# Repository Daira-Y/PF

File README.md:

# PF
Phamaceutical Water Analyzer

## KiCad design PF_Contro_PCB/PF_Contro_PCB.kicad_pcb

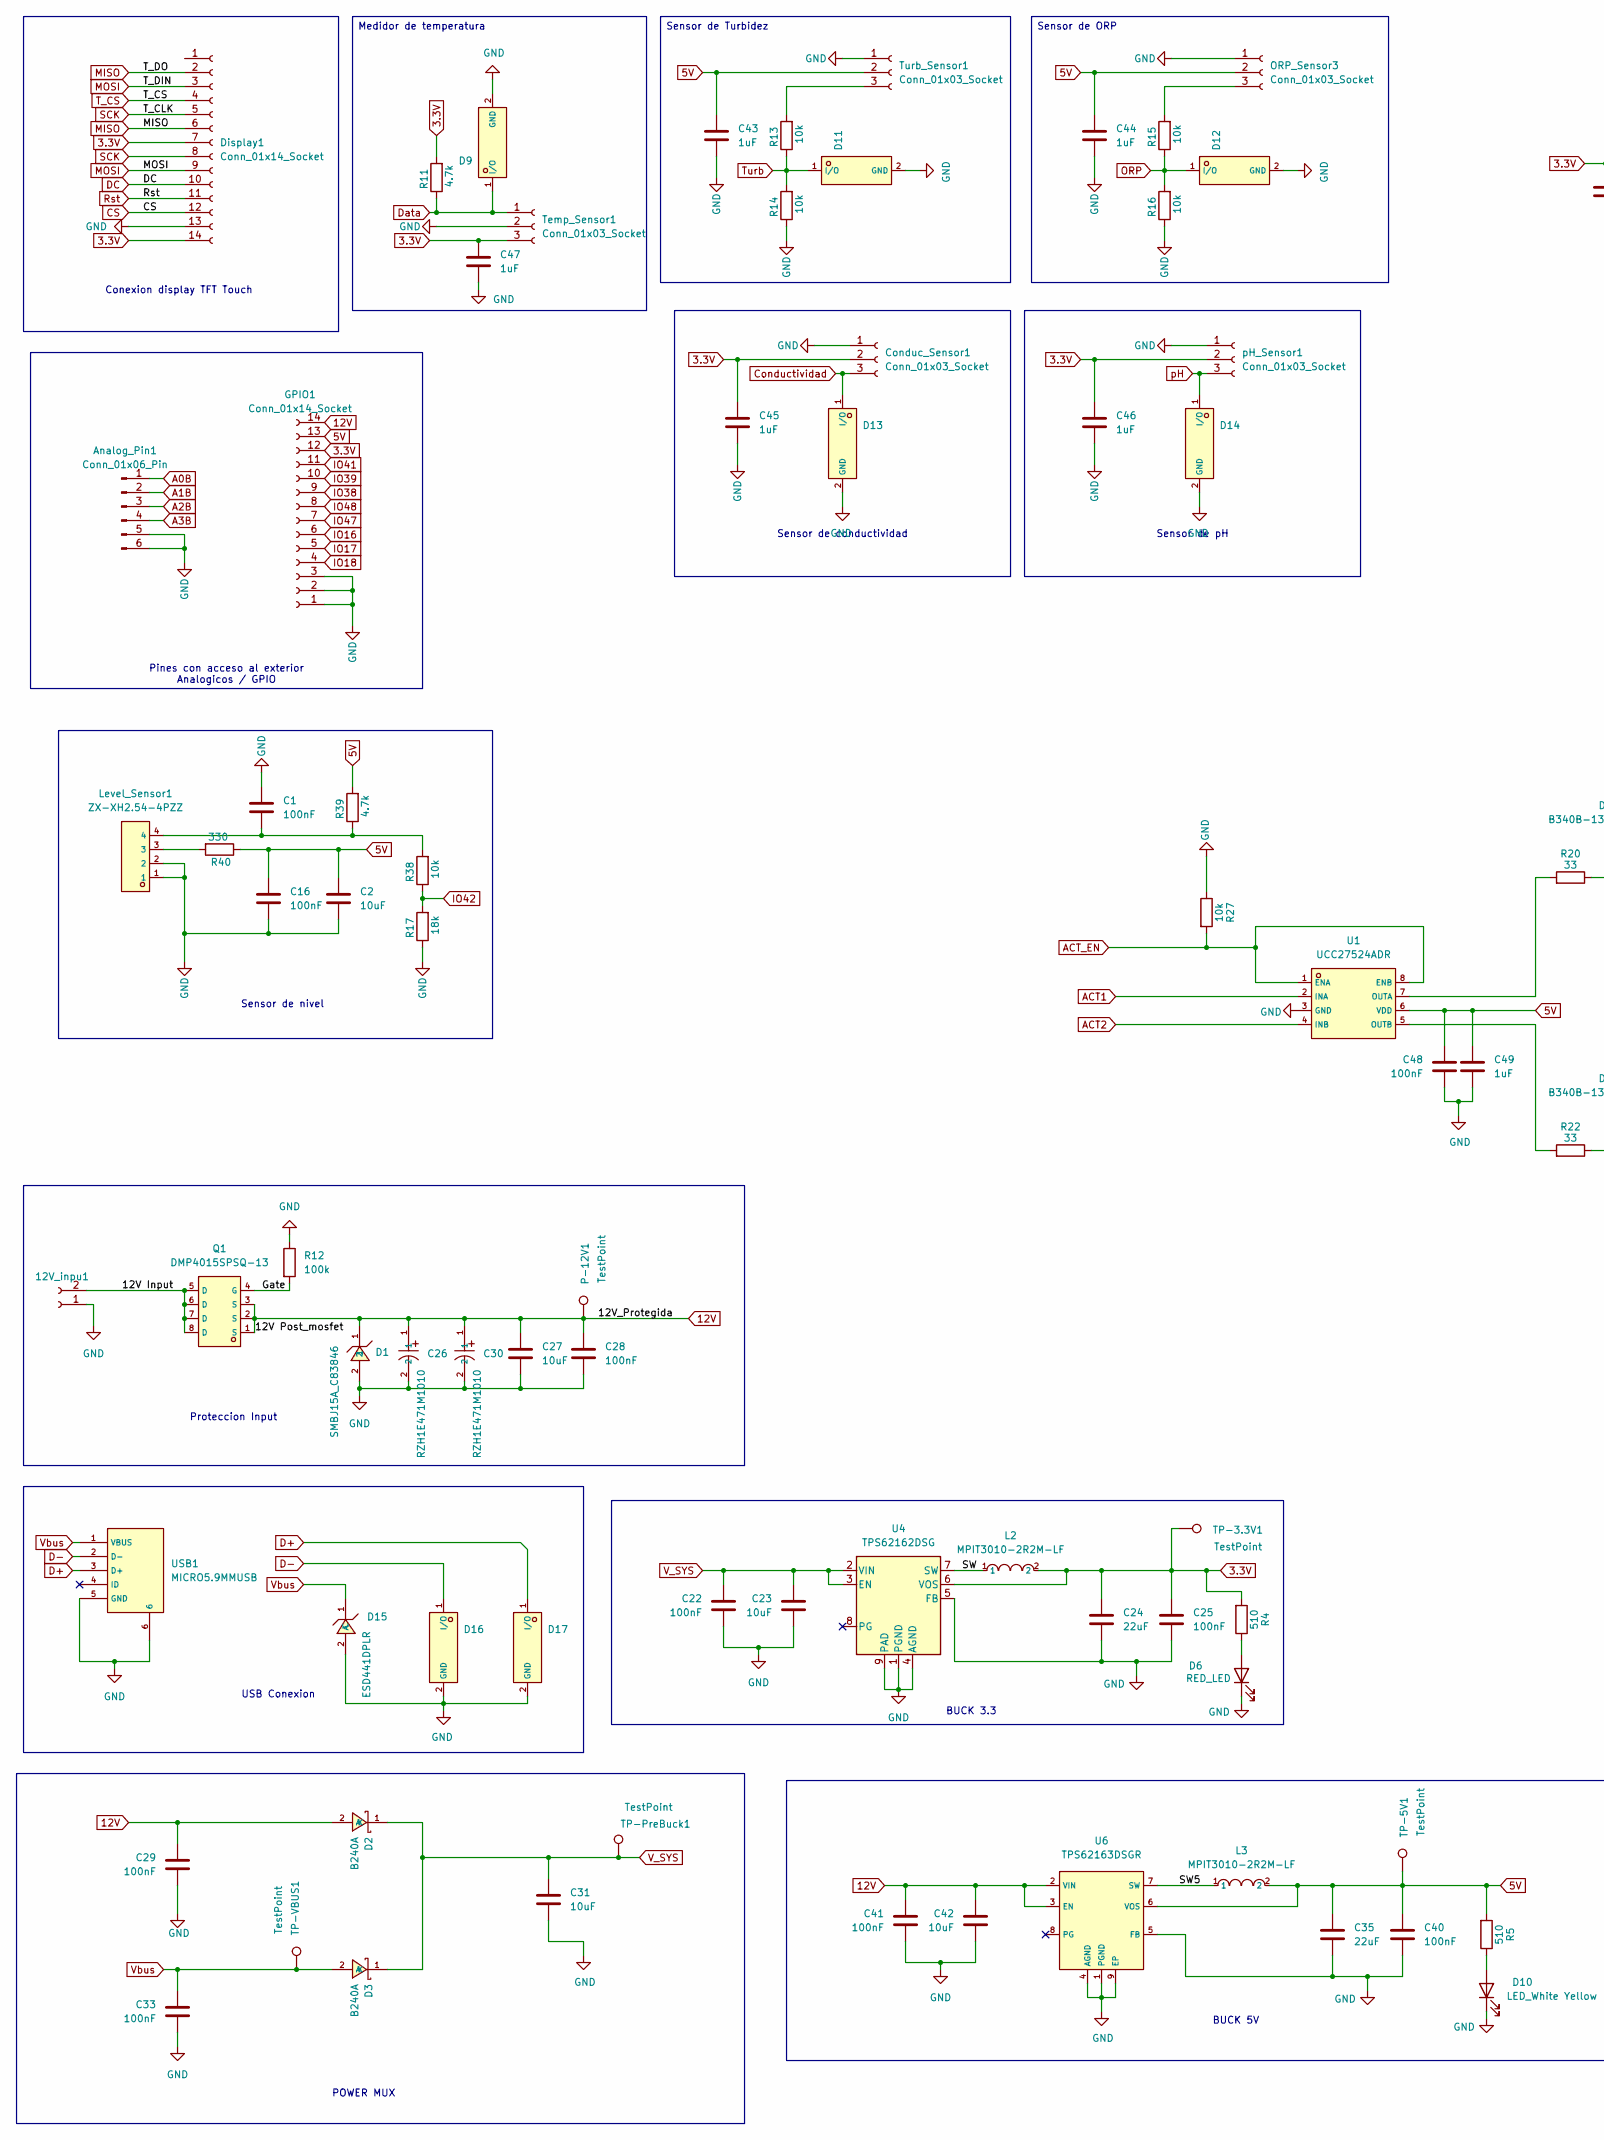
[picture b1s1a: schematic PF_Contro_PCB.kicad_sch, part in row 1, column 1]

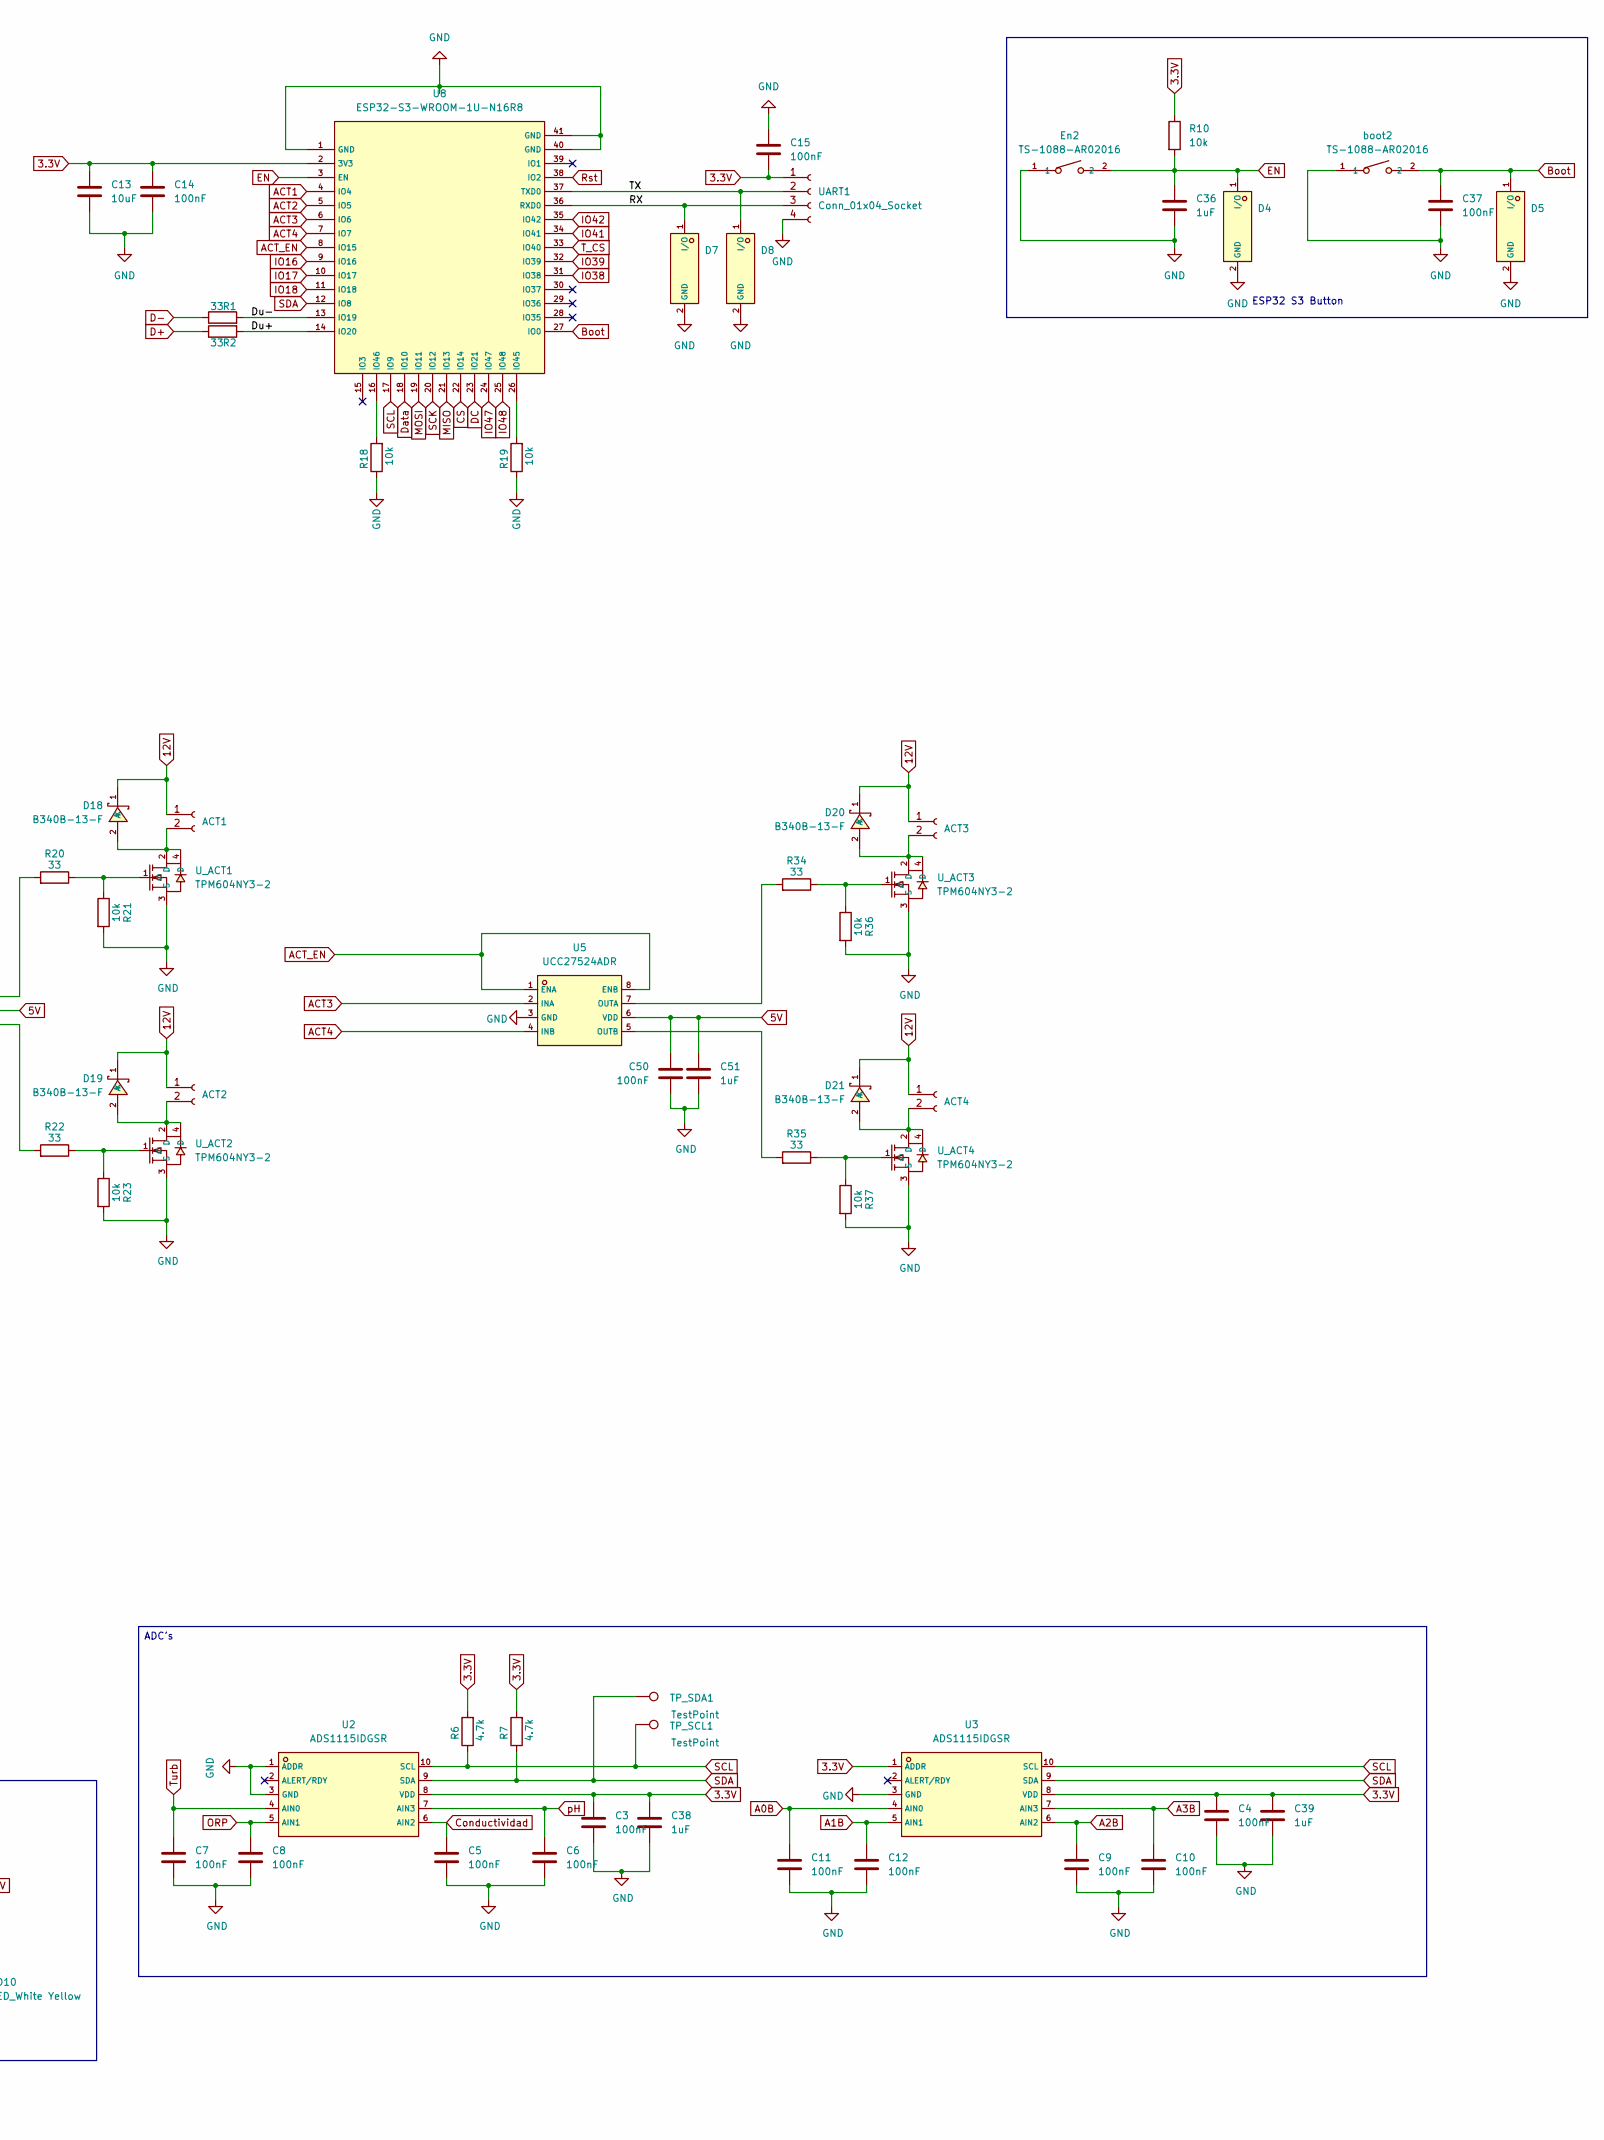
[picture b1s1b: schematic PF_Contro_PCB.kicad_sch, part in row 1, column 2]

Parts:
12V_inpu1: Conn_01x02_Socket; TerminalBlock_Phoenix_MKDS-1,5-2-5.08_1x02_P5.08mm_Horizont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
ACT1, ACT2, ACT3, ACT4: Conn_01x02_Socket; Molex_KK-254_AE-6410-02A_1x02_P2.54mm_Vertical
Analog_Pin1: Conn_01x06_Pin; PinSocket_1x06_P2.54mm_Vertical
C1, C16, C22, C25, C28, C29, C33, C40, C41, C48, C50: 100nF; C_0805_2012Metric
C2, C23, C27, C31, C42: 10uF; C_0805_2012Metric
C3, C4, C5, C6, C7, C8, C9, C10, C11, C12, C14, C15, C37: 100nF; C_0603_1608Metric
C13: 10uF; C_0603_1608Metric
C24, C35: 22uF; C_0805_2012Metric
C26, C30: RZH1E471M1010; C47117667_CAP-SMD_BD10_0-L10_3-W10_3-LS11_0-FD; LCSC C47117667
C36, C38, C39, C43, C44, C45, C46, C47, C49, C51: 1uF; C_0603_1608Metric
Conduc_Sensor1: Conn_01x03_Socket; Molex_KK-254_AE-6410-03A_1x03_P2.54mm_Vertical
D1: SMBJ15A_C83846; C83846_SMB_L4_6-W3_6-LS5_3-RD; LCSC C83846
D2, D3: B240A; C39358_SMA_L4_3-W2_6-LS5_2-RD; LCSC C39358
D4, D5, D7, D8, D9, D11, D12, D13, D14, D16, D17: ESD321DPYR_C2868952; C2868952_X1SON-2_L1_0-W0_6-P0_65-RD-1; LCSC C2868952
D6: RED_LED; LED_0603_1608Metric_Pad1.05x0.95mm_HandSolder
D10: LED_White Yellow; LED_0603_1608Metric_Pad1.05x0.95mm_HandSolder
D15: ESD441DPLR; C22427765_X2SON-2_L0_6-W0_3-P0_35; LCSC C22427765
D18, D19, D20, D21: B340B-13-F; C85099_SMB_L4_6-W3_6-LS5_3-RD; LCSC C85099
Display1: Conn_01x14_Socket; PinSocket_1x14_P2.54mm_Vertical
En2: TS-1088-AR02016; C720477_SW-SMD_L3_9-W3_0-P4_45; LCSC C720477
GPIO1: Conn_01x14_Socket; PinSocket_1x14_P2.54mm_Vertical
L2, L3: MPIT3010-2R2M-LF; C281241_IND-SMD_L3_0-W3_0_ABG03A; LCSC C281241
Level_Sensor1: ZX-XH2.54-4PZZ; C7429634_CONN-TH_4P-P2_50_4PIN; LCSC C7429634
ORP_Sensor3: Conn_01x03_Socket; Molex_KK-254_AE-6410-03A_1x03_P2.54mm_Vertical
P-12V1: TestPoint; Pin_D0.7mm_L6.5mm_W1.8mm_FlatFork
Q1: DMP4015SPSQ-13; C384564_POWERDI5060-8_L5_8-W4_9-P1_27-LS6_2-BL; LCSC C384564
R1, R2, R20, R22, R34, R35: 33; R_0603_1608Metric_Pad0.98x0.95mm_HandSolder
R4, R5: 510; R_0603_1608Metric_Pad0.98x0.95mm_HandSolder
R6, R7, R11, R39: 4.7k; R_0603_1608Metric_Pad0.98x0.95mm_HandSolder
R10, R13, R14, R15, R16, R18, R19, R21, R23, R27, R36, R37, R38: 10k; R_0603_1608Metric_Pad0.98x0.95mm_HandSolder
R12: 100k; R_0805_2012Metric_Pad1.20x1.40mm_HandSolder
R17: 18k; R_0603_1608Metric_Pad0.98x0.95mm_HandSolder
R40: 330; R_0603_1608Metric_Pad0.98x0.95mm_HandSolder
TP-3.3V1, TP-5V1: TestPoint; Pin_D0.7mm_L6.5mm_W1.8mm_FlatFork
TP-PreBuck1: TestPoint; Pin_D0.7mm_L6.5mm_W1.8mm_FlatFork
TP-VBUS1: TestPoint; Pin_D0.7mm_L6.5mm_W1.8mm_FlatFork
TP_SCL1: TestPoint; Pin_D0.7mm_L6.5mm_W1.8mm_FlatFork
TP_SDA1: TestPoint; Pin_D0.7mm_L6.5mm_W1.8mm_FlatFork
Temp_Sensor1: Conn_01x03_Socket; Molex_KK-254_AE-6410-03A_1x03_P2.54mm_Vertical
Turb_Sensor1: Conn_01x03_Socket; Molex_KK-254_AE-6410-03A_1x03_P2.54mm_Vertical
U1, U5: UCC27524ADR; C185857_SOIC-8_L4_9-W3_9-P1_27-LS6_0-BL; LCSC C185857
U2, U3: ADS1115IDGSR; C37593_MSOP-10_L3_0-W3_0-P0_50-LS5_0-BL; LCSC C37593
U4: TPS62162DSG; WSON-8-1EP_2x2mm_P0.5mm_EP0.9x1.6mm_ThermalVias
U6: TPS62163DSGR; C97534_WSON-8_L2_0-W2_0-P0_50-TL-EP; LCSC C97534
U8: ESP32-S3-WROOM-1U-N16R8; C3013946_WIRELM-SMD_ESP32-S3-WROOM-1U; LCSC C3013946
UART1: Conn_01x04_Socket; PinSocket_1x04_P2.54mm_Vertical
USB1: MICRO5.9MMUSB; C393940_MICRO-USB-SMD_5P-P0_65-H-F_MICRO5_9MMUSB; LCSC C393940
U_ACT1, U_ACT2, U_ACT3, U_ACT4: TPM604NY3-2; C7472938_SOT-223-3_L6_5-W3_4-P2_30-LS7_0-BR; LCSC C7472938
boot2: TS-1088-AR02016; C720477_SW-SMD_L3_9-W3_0-P4_45; LCSC C720477
pH_Sensor1: Conn_01x03_Socket; Molex_KK-254_AE-6410-03A_1x03_P2.54mm_Vertical

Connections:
3.3V: C3.1, C4.1, C13.1, C14.1, C15.2, C24.1, C25.1, C38.1, C39.1, C45.1, C46.1, C47.1, Conduc_Sensor1.2, Display1.7, Display1.14, GPIO1.12, L2.2, R4.2, R6.2, R7.2, R10.1, R11.2, TP-3.3V1.1, Temp_Sensor1.3, U2.8 (VDD), U3.1 (ADDR), U3.8 (VDD), U4.6 (VOS), U8.2 (3V3), UART1.1, pH_Sensor1.2
5V: C2.1, C16.1, C35.1, C40.1, C43.1, C44.1, C48.1, C49.1, C50.1, C51.1, GPIO1.13, L3.2, ORP_Sensor3.2, R5.2, R39.2, R40.1, TP-5V1.1, Turb_Sensor1.2, U1.6 (VDD), U5.6 (VDD), U6.6 (VOS)
12V: ACT1.1, ACT2.1, ACT3.1, ACT4.1, C26.1, C27.1, C28.1, C29.1, C30.1, C41.1, C42.1, D1.1, D2.2 (A), D18.1 (K), D19.1 (K), D20.1 (K), D21.1 (K), GPIO1.14, P-12V1.1, Q1.1 (S), Q1.2 (S), Q1.3 (S), U6.2 (VIN), U6.3 (EN)
/12V Input: 12V_inpu1.2, Q1.5 (D), Q1.6 (D), Q1.7 (D), Q1.8 (D)
/Du+: R2.2, U8.14 (IO20)
/Du-: R1.2, U8.13 (IO19)
/Gate: Q1.4 (G), R12.2
/RX: D7.1 (I/O), U8.36 (RXD0), UART1.3
/SW: L2.1, U4.7 (SW)
/SW5: L3.1, U6.7 (SW)
/TX: D8.1 (I/O), U8.37 (TXD0), UART1.2
A0B: Analog_Pin1.1, C11.1, U3.4 (AIN0)
A1B: Analog_Pin1.2, C12.1, U3.5 (AIN1)
A2B: Analog_Pin1.3, C9.1, U3.6 (AIN2)
A3B: Analog_Pin1.4, C10.1, U3.7 (AIN3)
ACT1: U1.2 (INA), U8.4 (IO4)
ACT2: U1.4 (INB), U8.5 (IO5)
ACT3: U5.2 (INA), U8.6 (IO6)
ACT4: U5.4 (INB), U8.7 (IO7)
ACT_EN: R27.2, U1.1 (ENA), U1.8 (ENB), U5.1 (ENA), U5.8 (ENB), U8.8 (IO15)
Boot: C37.1, D5.1 (I/O), U8.27 (IO0), boot2.2
CS: Display1.12, U8.22 (IO14)
Conductividad: C5.1, Conduc_Sensor1.3, D13.1 (I/O), U2.6 (AIN2)
D+: D17.1 (I/O), R2.1, USB1.3 (D+)
D-: D16.1 (I/O), R1.1, USB1.2 (D-)
DC: Display1.10, U8.23 (IO21)
Data: D9.1 (I/O), R11.1, Temp_Sensor1.1, U8.18 (IO10)
EN: C36.1, D4.1 (I/O), En2.2, R10.2, U8.3 (EN)
GND: 12V_inpu1.1, Analog_Pin1.5, Analog_Pin1.6, C1.2, C2.2, C3.2, C4.2, C5.2, C6.2, C7.2, C8.2, C9.2, C10.2, C11.2, C12.2, C13.2, C14.2, C15.1, C16.2, C22.2, C23.2, C24.2, C25.2, C26.2, C27.2, C28.2, C29.2, C30.2, C31.2, C33.2, C35.2, C36.2, C37.2, C38.2, C39.2, C40.2, C41.2, C42.2, C43.2, C44.2, C45.2, C46.2, C47.2, C48.2, C49.2, C50.2, C51.2, Conduc_Sensor1.1, D1.2, D4.2 (GND), D5.2 (GND), D6.1 (K), D7.2 (GND), D8.2 (GND), D9.2 (GND), D10.1 (K), D11.2 (GND), D12.2 (GND), D13.2 (GND), D14.2 (GND), D15.2 (A), D16.2 (GND), D17.2 (GND), Display1.13, En2.1, GPIO1.1, GPIO1.2, GPIO1.3, Level_Sensor1.1, Level_Sensor1.2, ORP_Sensor3.1, R12.1, R14.1, R16.1, R17.1, R18.1, R19.1, R21.2, R23.2, R27.1, R36.2, R37.2, Temp_Sensor1.2, Turb_Sensor1.1, U1.3 (GND), U2.1 (ADDR), U2.3 (GND), U3.3 (GND), U4.1 (PGND), U4.4 (AGND), U4.5 (FB), U4.9 (PAD), U5.3 (GND), U6.1 (PGND), U6.4 (AGND), U6.5 (FB), U6.9 (EP), U8.1 (GND), U8.40 (GND), U8.41 (GND), UART1.4, USB1.5 (GND), USB1.6, U_ACT1.3 (S), U_ACT2.3 (S), U_ACT3.3 (S), U_ACT4.3 (S), boot2.1, pH_Sensor1.1
IO16: GPIO1.6, U8.9 (IO16)
IO17: GPIO1.5, U8.10 (IO17)
IO18: GPIO1.4, U8.11 (IO18)
IO38: GPIO1.9, U8.31 (IO38)
IO39: GPIO1.10, U8.32 (IO39)
IO41: GPIO1.11, U8.34 (IO41)
IO42: R17.2, R38.1, U8.35 (IO42)
IO47: GPIO1.7, U8.24 (IO47)
IO48: GPIO1.8, U8.25 (IO48)
MISO: Display1.2, Display1.6, U8.21 (IO13)
MOSI: Display1.3, Display1.9, U8.19 (IO11)
unnamed: ACT1.2, D18.2 (A), U_ACT1.2 (D), U_ACT1.4 (D)
unnamed: ACT2.2, D19.2 (A), U_ACT2.2 (D), U_ACT2.4 (D)
unnamed: ACT3.2, D20.2 (A), U_ACT3.2 (D), U_ACT3.4 (D)
unnamed: ACT4.2, D21.2 (A), U_ACT4.2 (D), U_ACT4.4 (D)
unnamed: C1.1, Level_Sensor1.4, R38.2, R39.1
unnamed: D6.2 (A), R4.1
unnamed: D10.2 (A), R5.1
unnamed: Level_Sensor1.3, R40.2
unnamed: ORP_Sensor3.3, R15.2
unnamed: R13.2, Turb_Sensor1.3
unnamed: R20.2, U1.7 (OUTA)
unnamed: R22.2, U1.5 (OUTB)
unnamed: R34.2, U5.7 (OUTA)
unnamed: R35.2, U5.5 (OUTB)
unnamed: R19.2, U8.26 (IO45)
unnamed: R18.2, U8.16 (IO46)
unnamed: R20.1, R21.1, U_ACT1.1 (G)
unnamed: R22.1, R23.1, U_ACT2.1 (G)
unnamed: R34.1, R36.1, U_ACT3.1 (G)
unnamed: R35.1, R37.1, U_ACT4.1 (G)
ORP: C8.1, D12.1 (I/O), R15.1, R16.2, U2.5 (AIN1)
Rst: Display1.11, U8.38 (IO2)
SCK: Display1.5, Display1.8, U8.20 (IO12)
SCL: R6.1, TP_SCL1.1, U2.10 (SCL), U3.10 (SCL), U8.17 (IO9)
SDA: R7.1, TP_SDA1.1, U2.9 (SDA), U3.9 (SDA), U8.12 (IO8)
T_CS: Display1.4, U8.33 (IO40)
Turb: C7.1, D11.1 (I/O), R13.1, R14.2, U2.4 (AIN0)
V_SYS: C22.1, C23.1, C31.1, D2.1 (K), D3.1 (K), TP-PreBuck1.1, U4.2 (VIN), U4.3 (EN)
Vbus: C33.1, D3.2 (A), D15.1 (C), TP-VBUS1.1, USB1.1 (VBUS)
pH: C6.1, D14.1 (I/O), U2.7 (AIN3), pH_Sensor1.3

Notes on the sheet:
BUCK 5V
POWER MUX
ESP32 S3 Button
Conexion display TFT Touch
BUCK 3.3
Sensor de nivel
USB Conexion
Proteccion Input
Medidor de temperatura
Sensor de conductividad
Sensor de ORP
Pines con acceso al exterior Analogicos / GPIO
Sensor de Turbidez
ADC's
Sensor de pH

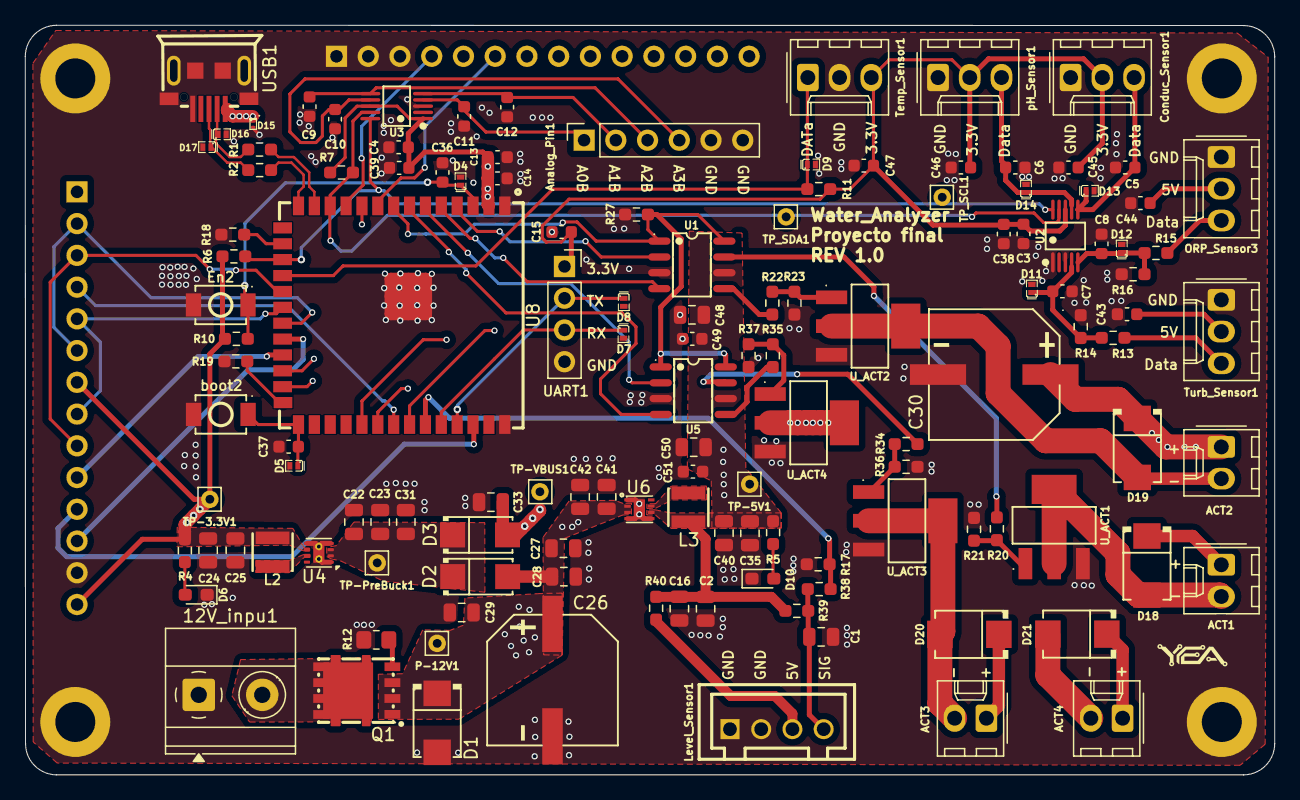
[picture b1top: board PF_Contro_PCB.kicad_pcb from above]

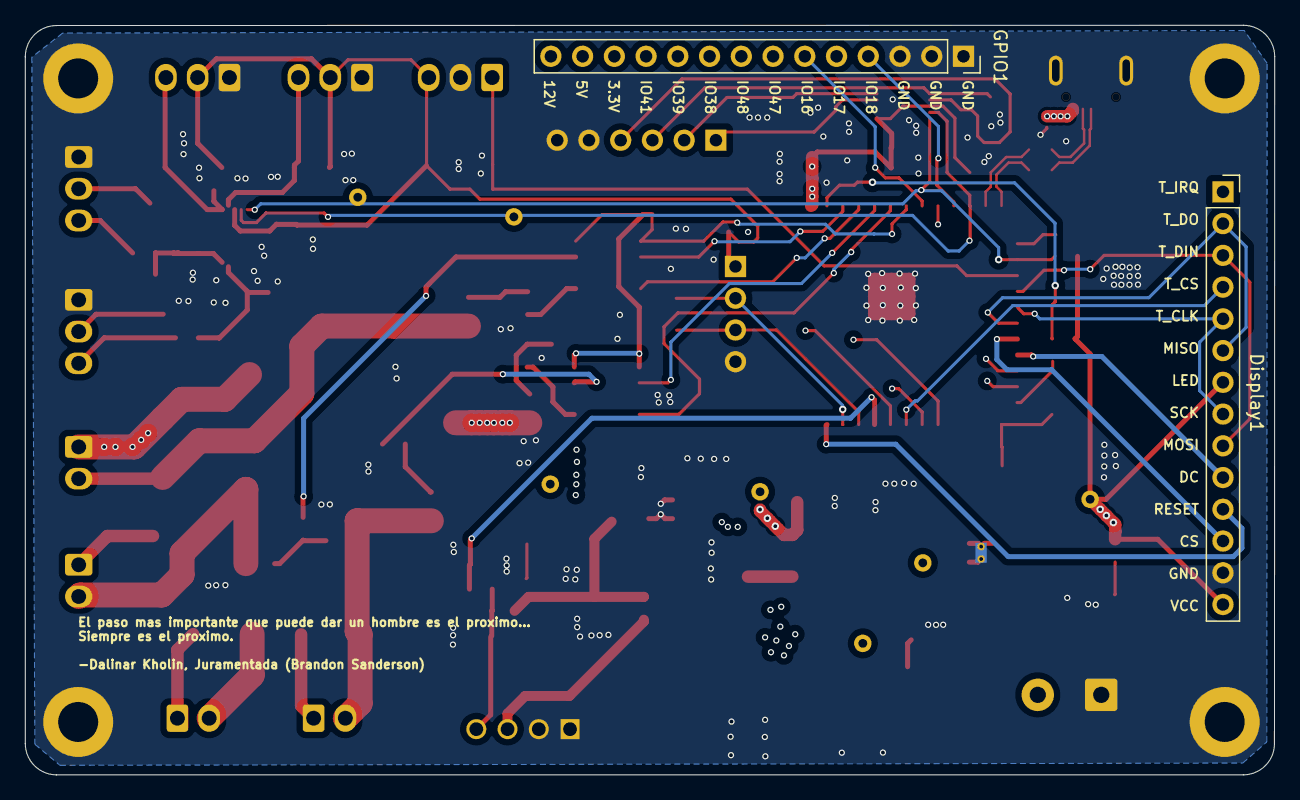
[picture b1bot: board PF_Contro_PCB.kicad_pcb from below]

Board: 4 copper layers, 100.0 x 60.0 mm, 132 parts (2 on the bottom side), 70 nets.

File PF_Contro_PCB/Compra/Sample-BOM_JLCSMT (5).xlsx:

Comment | Designator | Footprint | JLCPCB Part #（optional）
100nF | C40,C48,C22,C25,C50,C28,C1,C16,C29,C41,C33 | C_0805_2012Metric
ESD321DPYR_C2868952 | D4,D12,D13,D9,D11,D14,D16,D17,D7,D8,D5 | C2868952_X1SON-2_L1_0-W0_6-P0_65-RD-1
10k | R38,R36,R27,R37,R16,R10,R18,R19,R23,R13,R14,R21,R15 | R_0603_1608Metric_Pad0.98x0.95mm_HandSolder
TPM604NY3-2 | U_ACT1,U_ACT3,U_ACT4,U_ACT2 | C7472938_SOT-223-3_L6_5-W3_4-P2_30-LS7_0-BR
100nF | C37,C10,C12,C8,C11,C7,C9,C14,C5,C6,C15,C4,C3 | C_0603_1608Metric
1uF | C38,C44,C49,C47,C51,C46,C39,C45,C36,C43 | C_0603_1608Metric
B340B-13-F | D20,D19,D18,D21 | C85099_SMB_L4_6-W3_6-LS5_3-RD
510 | R4,R5 | R_0603_1608Metric_Pad0.98x0.95mm_HandSolder
TS-1088-AR02016 | boot2,En2 | C720477_SW-SMD_L3_9-W3_0-P4_45
TestPoint | TP-5V1,TP_SCL1,P-12V1,TP_SDA1,TP-3.3V1,TP-PreBuck1,TP-VBUS1 | Pin_D0.7mm_L6.5mm_W1.8mm_FlatFork
MPIT3010-2R2M-LF | L2,L3 | C281241_IND-SMD_L3_0-W3_0_ABG03A
UCC27524ADR | U5,U1 | C185857_SOIC-8_L4_9-W3_9-P1_27-LS6_0-BL
33 | R20,R35,R1,R2,R22,R34 | R_0603_1608Metric_Pad0.98x0.95mm_HandSolder
330 | R40 | R_0603_1608Metric_Pad0.98x0.95mm_HandSolder
SMBJ15A_C83846 | D1 | C83846_SMB_L4_6-W3_6-LS5_3-RD
ESP32-S3-WROOM-1U-N16R8 | U8 | C3013946_WIRELM-SMD_ESP32-S3-WROOM-1U
22uF | C24,C35 | C_0805_2012Metric
ADS1115IDGSR | U2,U3 | C37593_MSOP-10_L3_0-W3_0-P0_50-LS5_0-BL
10uF | C23,C31,C27,C2,C42 | C_0805_2012Metric
DMP4015SPSQ-13 | Q1 | C384564_POWERDI5060-8_L5_8-W4_9-P1_27-LS6_2-BL
B240A | D2,D3 | C39358_SMA_L4_3-W2_6-LS5_2-RD
RZH1E471M1010 | C30,C26 | C47117667_CAP-SMD_BD10_0-L10_3-W10_3-LS11_0-FD
LED_White Yellow | D10 | LED_0603_1608Metric_Pad1.05x0.95mm_HandSolder
4.7k | R39,R6,R7,R11 | R_0603_1608Metric_Pad0.98x0.95mm_HandSolder
RED_LED | D6 | LED_0603_1608Metric_Pad1.05x0.95mm_HandSolder
Conn_01x02_Socket | ACT4,ACT3,ACT2,ACT1 | Molex_KK-254_AE-6410-02A_1x02_P2.54mm_Vertical
MICRO5.9MMUSB | USB1 | C393940_MICRO-USB-SMD_5P-P0_65-H-F_MICRO5_9MMUSB
ESD441DPLR | D15 | C22427765_X2SON-2_L0_6-W0_3-P0_35
TPS62162DSG | U4 | WSON-8-1EP_2x2mm_P0.5mm_EP0.9x1.6mm_ThermalVias
Conn_01x03_Socket | ORP_Sensor3,Temp_Sensor1,Turb_Sensor1,pH_Sensor1,Conduc_Sensor1 | Molex_KK-254_AE-6410-03A_1x03_P2.54mm_Vertical
TPS62163DSGR | U6 | C97534_WSON-8_L2_0-W2_0-P0_50-TL-EP
100k | R12 | R_0805_2012Metric_Pad1.20x1.40mm_HandSolder
Conn_01x06_Pin | Analog_Pin1 | PinSocket_1x06_P2.54mm_Vertical
Conn_01x04_Socket | UART1 | PinSocket_1x04_P2.54mm_Vertical
ZX-XH2.54-4PZZ | Level_Sensor1 | C7429634_CONN-TH_4P-P2_50_4PIN
18k | R17 | R_0603_1608Metric_Pad0.98x0.95mm_HandSolder
Conn_01x02_Socket | 12V_inpu1 | TerminalBlock_Phoenix_MKDS-1,5-2-5.08_1x02_P5.08mm_Horizontal
10uF | C13 | C_0603_1608Metric
Conn_01x14_Socket | GPIO1,Display1 | PinSocket_1x14_P2.54mm_Vertical
